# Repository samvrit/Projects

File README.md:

<h1>Projects</h1>
- <b>1-D Localization:</b> This is a 1-D Localization Problem. The map is given. User has to input the sensor values (0s and/or 1s). Once the robot figures out where it started, it will display the same. '3' is the starting point and '2' is the ending point. Accuracy of sensors/actuators is not considered in this algorithm (ie., probability of sensor and actuator are considered 1).   
- <b>Bluetooth-Controlled Modular Vehicle:</b> This is the software for a bluetooth-controlled modular vehicle (one main vehicle and two auxiliary vehicles).   
- <b>Certificates:</b> This directory contains a few important certificates.   
- <b>Electronic Dartboard:</b> This is a project aimed to develop an electronic dartboard which can output the score to a server every time a dart hits a target. The output is displayed on a remote computer.   
- <b>Grid Solving Robot:</b> An international level robotics competition held at IIT Bombay. The robot is given specific coordinates on a grid, to which it is supposed to navigate, and display the colour code of the surrounding four squares. The squares may have white colour or no colour, which the robot is supposed to indicate using four on-board LEDs.   
- <b>Line Follower using Image Processing</b>   
- <b>MATLAB Resultant Mass:</b> A MATLAB program to find the resultant mass for balancing of rotating masses on common axis (planar).   
- <b>Morse Code Reader Robot:</b> A national level robotics competition held at NIT-K Suratkal, Karnataka. The Robot is supposed to traverse a line containing several combinations of dots and dashes. A combination of five (dots and/or dashes) represents a number in Morse code. The robot is supposed to traverse the arena and add up all the numbers  represented in Morse code, and in the end, display the sum.   
- <b>PID Line Follower:</b> Line follower robot algorithm which uses PID to find the centre of the black line on a white background   
- <b>RFID Check-in System:</b> This project uses RFID tags to check-in a user into a database. This project can be applied to any area which requires checking-in at different places under the same Wi-Fi network.   
- <b>Supernumerary Robotic Limbs (Final Year Project):</b> Supernumerary Robotic Arms is a pair of low cost multi-purpose Robotic arms with 4 DoFs in each arm. The Robot is extendable in terms of functionality by attaching suitable end-effectors depending on the application. The actuators can be controlled wirelessly using nRF24L01 radio modules. Motion Planning is done using geometrically derived inverse kinematics. Mathematical Model and Simulations have been carried out using MATLAB Simulink and Robotics Toolbox for MATLAB. The robot description model (URDF) and the corresponding MoveIt! configuration package have also been developed for ROS. This project was funded by the IEEE University Partnership Program ($1500). Mentor: <a href="http://www.mecheng.iisc.ernet.in/~asitava/" target="_blank">Prof. Ashitava Ghosal</a>, IISc.

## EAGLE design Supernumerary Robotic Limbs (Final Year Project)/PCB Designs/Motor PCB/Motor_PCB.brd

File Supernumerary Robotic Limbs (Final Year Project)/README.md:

<h1>Supernumerary Robotic Limbs - Final Year Project</h1>
Supernumerary Robotic Arms is a pair of low cost multi-purpose Robotic arms with 4 DoFs in each arm. The Robot is extendable in terms of functionality by attaching suitable end-effectors depending on the application. The actuators can be controlled wirelessly using nRF24L01 radio modules. Motion Planning is done using geometrically derived inverse kinematics. Mathematical Model and Simulations have been carried out using MATLAB Simulink and Robotics Toolbox for MATLAB. The robot description model (URDF) and the corresponding MoveIt! configuration package have also been developed for ROS. This project was funded by the IEEE University Partnership Program ($1500). Mentor: <a href="http://www.mecheng.iisc.ernet.in/~asitava/" target="_blank">Prof. Ashitava Ghosal</a>, IISc.

A <a href="http://ieeexplore.ieee.org/xpl/articleDetails.jsp?arnumber=7283889" target="_blank">paper</a> was published on the mechanical design and kinematic model of the robot.

The robot is currently a stationary one, but it is intended to be a mobile platform, which can be worn by the user like a backpack.

Applications of this kind of robots can be seen in tasks that can be semi-automated, such as in assembly of aeroplanes, wiring of control boxes, etc.

The project was inspired by the work done by students of MIT under Prof. Harry Asada.

Videos:

1. <a href="https://www.youtube.com/watch?v=1jS6DkzcwM0" target="_blank">Robot in action</a>
2. <a href="https://www.youtube.com/watch?v=-V_I5MpTWcI" target="_blank">Robot Inverse Kinematics Simulation (MATLAB Robotics Toolbox)</a>
3. <a href="https://www.youtube.com/watch?v=2IG5NMGldtQ" target="_blank">Paper presentation on the project at the 20th International Conference on Methods and Models in Automation and Robotics</a>
4. <a href="https://www.youtube.com/watch?v=e1p7m6lmJI8" target="_blank">Robot writing the word "IISc"</a>

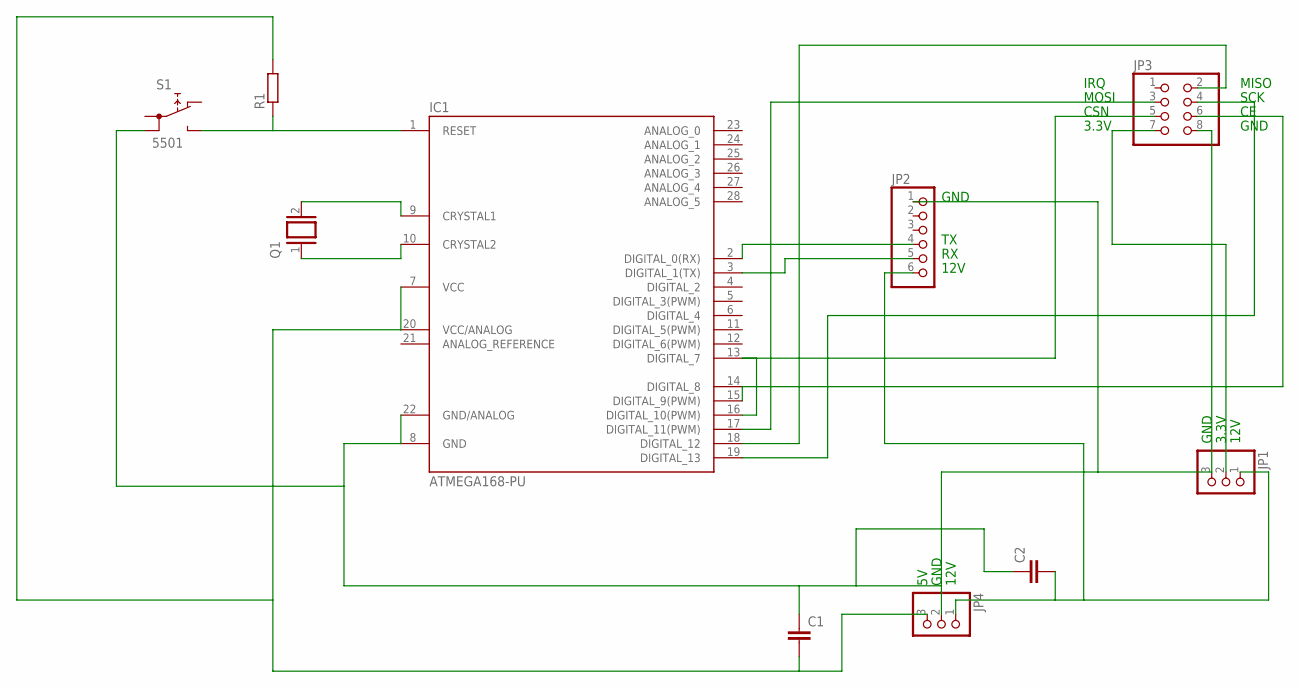
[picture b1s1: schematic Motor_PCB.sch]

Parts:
C1, C2: C2,5-3; C2.5-3
IC1: ATMEGA168-PU; DIL28-3
JP1, JP4: PINHD-1X3; 1X03
JP2: PINHD-1X6; 1X06
JP3: PINHD-2X4; 2X04
Q1: XTAL/S; QS
R1: R0207/10; 0207/10
S1: 5501

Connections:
unnamed: IC1.9 (CRYSTAL1), Q1.2
unnamed: IC1.10 (CRYSTAL2), Q1.1
unnamed: C1.2, IC1.7 (VCC), IC1.20 (VCC/ANALOG), JP4.3, R1.2
unnamed: C1.1, C2.1, IC1.8 (GND), IC1.22 (GND/ANALOG), JP1.3, JP2.1, JP3.8, JP4.2, S1.1B
unnamed: IC1.1 (RESET), R1.1, S1.NO
unnamed: C2.2, JP1.1, JP2.6, JP4.1
unnamed: IC1.17 (DIGITAL_11(PWM)), JP3.3
unnamed: IC1.18 (DIGITAL_12), JP3.2
unnamed: IC1.13 (DIGITAL_7), IC1.16 (DIGITAL_10(PWM)), JP3.5
unnamed: IC1.2 (DIGITAL_0(RX)), JP2.4
unnamed: IC1.3 (DIGITAL_1(TX)), JP2.5
unnamed: JP1.2, JP3.7
unnamed: IC1.14 (DIGITAL_8), IC1.15 (DIGITAL_9(PWM)), JP3.6
unnamed: IC1.19 (DIGITAL_13), JP3.4

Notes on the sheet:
12V
3.3V
GND
CSN
SCK
MOSI
MISO
IRQ

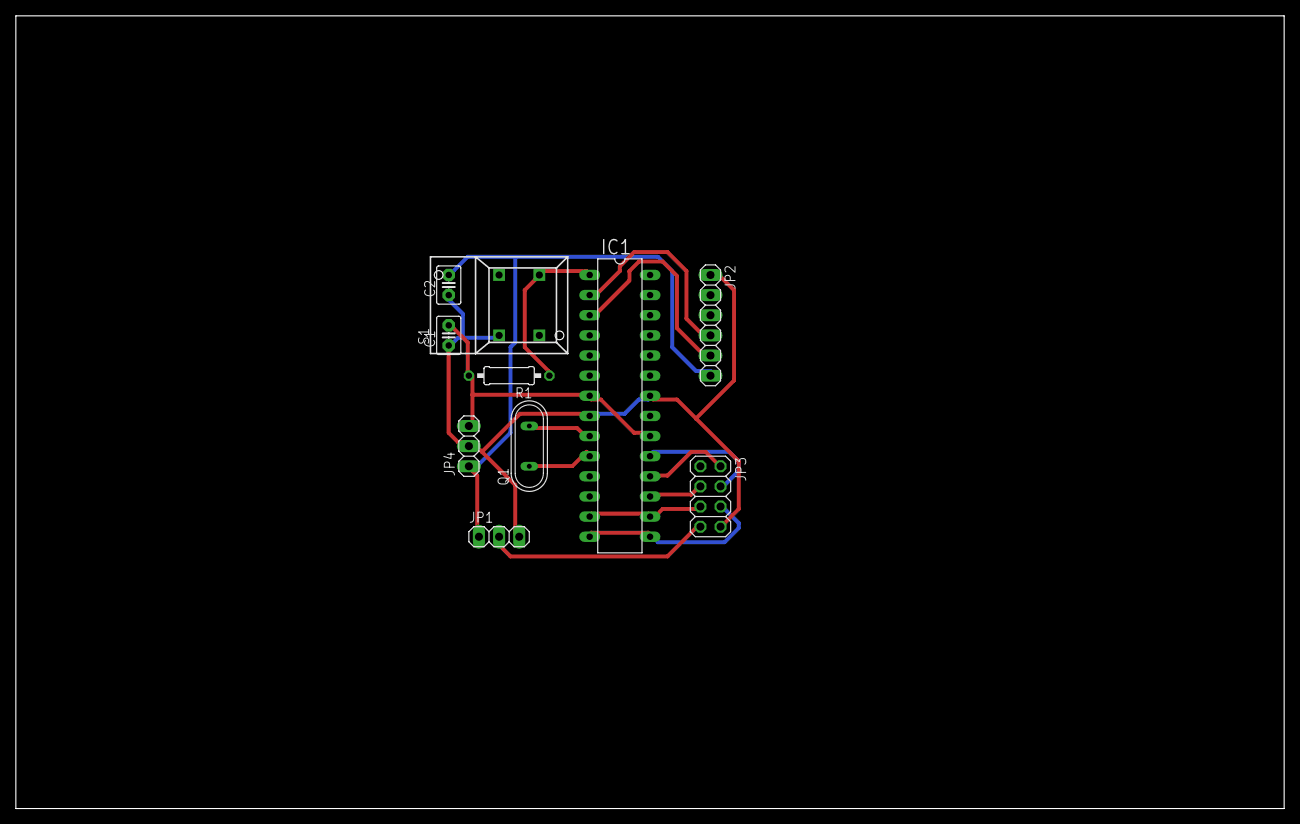
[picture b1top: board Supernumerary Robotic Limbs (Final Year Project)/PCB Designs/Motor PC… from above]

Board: 2 copper layers, 160.0 x 100.0 mm, 10 parts (0 on the bottom side), 14 nets.

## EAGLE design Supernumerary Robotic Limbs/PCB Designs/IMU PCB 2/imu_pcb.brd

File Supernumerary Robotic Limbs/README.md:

Supernumerary Robotic Arms is a pair of low cost multi-purpose Robotic arms with 4 DoFs in each arm. The Robot is extendable in terms of functionality by attaching suitable end-effectors depending on the application. The actuators can be controlled wirelessly using NRF24L01 radio modules. Motion Planning is done using geometrically derived inverse kinematics. Mathematical Model and Simulations have been carried out using MATLAB Simulink and Robotics Toolbox for MATLAB.  This project was funded by the IEEE University Partnership Program ($1500).

The robot is currently a stationary one, but it is intended to be a mobile platform, which can be worn by the user like a backpack.

Applications of this kind of robots can be seen in tasks that can be semi-automated, such as in assembly of aeroplanes, wiring of control boxes, etc.

The project was inspired by the work done by students of MIT under Prof. Harry Asada.

Videos:

1. Robot in action: https://www.youtube.com/watch?v=1jS6DkzcwM0
2. Robot Inverse Kinematics Simulation (MATLAB Robotics Toolbox): https://www.youtube.com/watch?v=-V_I5MpTWcI
3. Paper presentation on the project at the 20th International Conference on Methods and Models in Automation and Robotics: https://www.youtube.com/watch?v=2IG5NMGldtQ

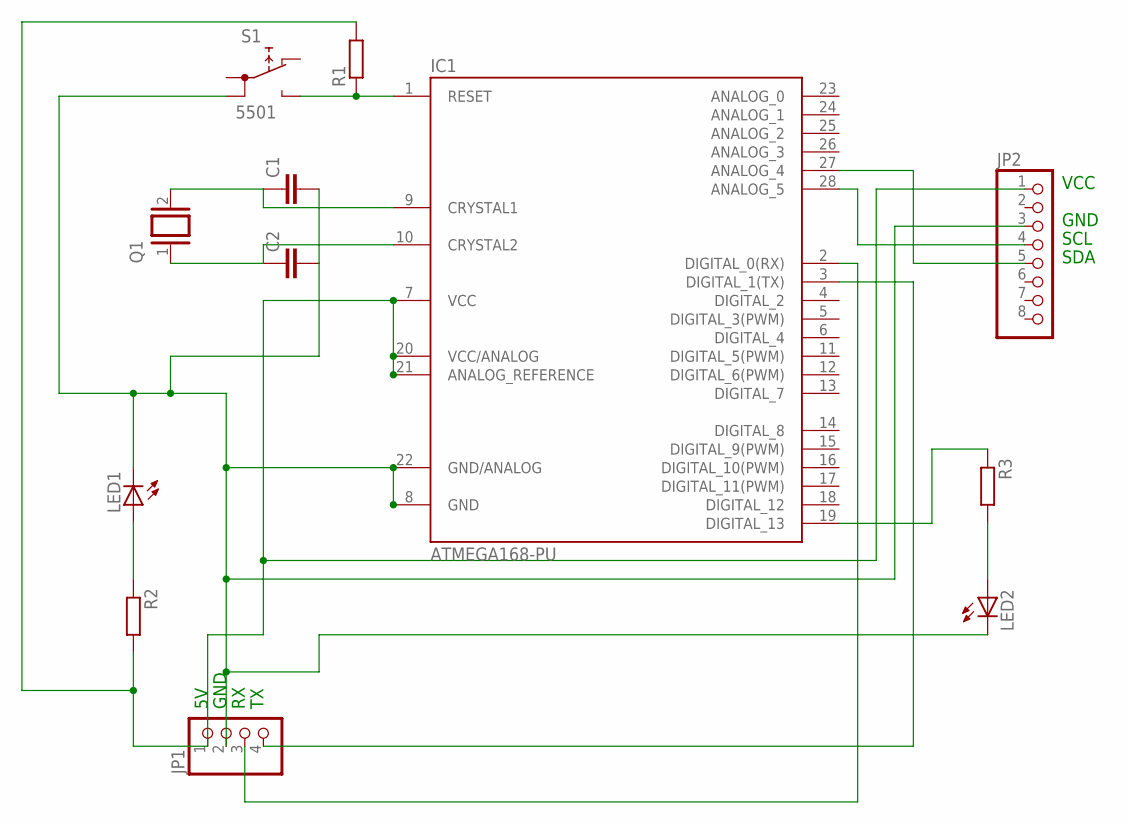
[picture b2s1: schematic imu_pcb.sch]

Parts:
C1, C2: C2.5/2; C2.5-2
IC1: ATMEGA168-PU; DIL28-3
JP1: PINHD-1X4; 1X04
JP2: PINHD-1X8; 1X08
LED1, LED2: LED3MM
Q1: XTAL/S; QS
R1, R2, R3: R0204/7; 0204/7
S1: 5501

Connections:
unnamed: IC1.1 (RESET), R1.1, S1.NO
unnamed: IC1.7 (VCC), IC1.20 (VCC/ANALOG), IC1.21 (ANALOG_REFERENCE), JP1.1, JP2.1, R1.2, R2.2
unnamed: LED1.A, R2.1
unnamed: C1.1, IC1.9 (CRYSTAL1), Q1.2
unnamed: C2.1, IC1.10 (CRYSTAL2), Q1.1
unnamed: IC1.2 (DIGITAL_0(RX)), JP1.3
unnamed: IC1.3 (DIGITAL_1(TX)), JP1.4
unnamed: C1.2, C2.2, IC1.8 (GND), IC1.22 (GND/ANALOG), JP1.2, JP2.3, LED1.K (C), LED2.K (C), S1.1B
unnamed: IC1.27 (ANALOG_4), JP2.5
unnamed: IC1.28 (ANALOG_5), JP2.4
unnamed: IC1.19 (DIGITAL_13), R3.1
unnamed: LED2.A, R3.2

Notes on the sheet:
GND
VCC
SCL
SDA

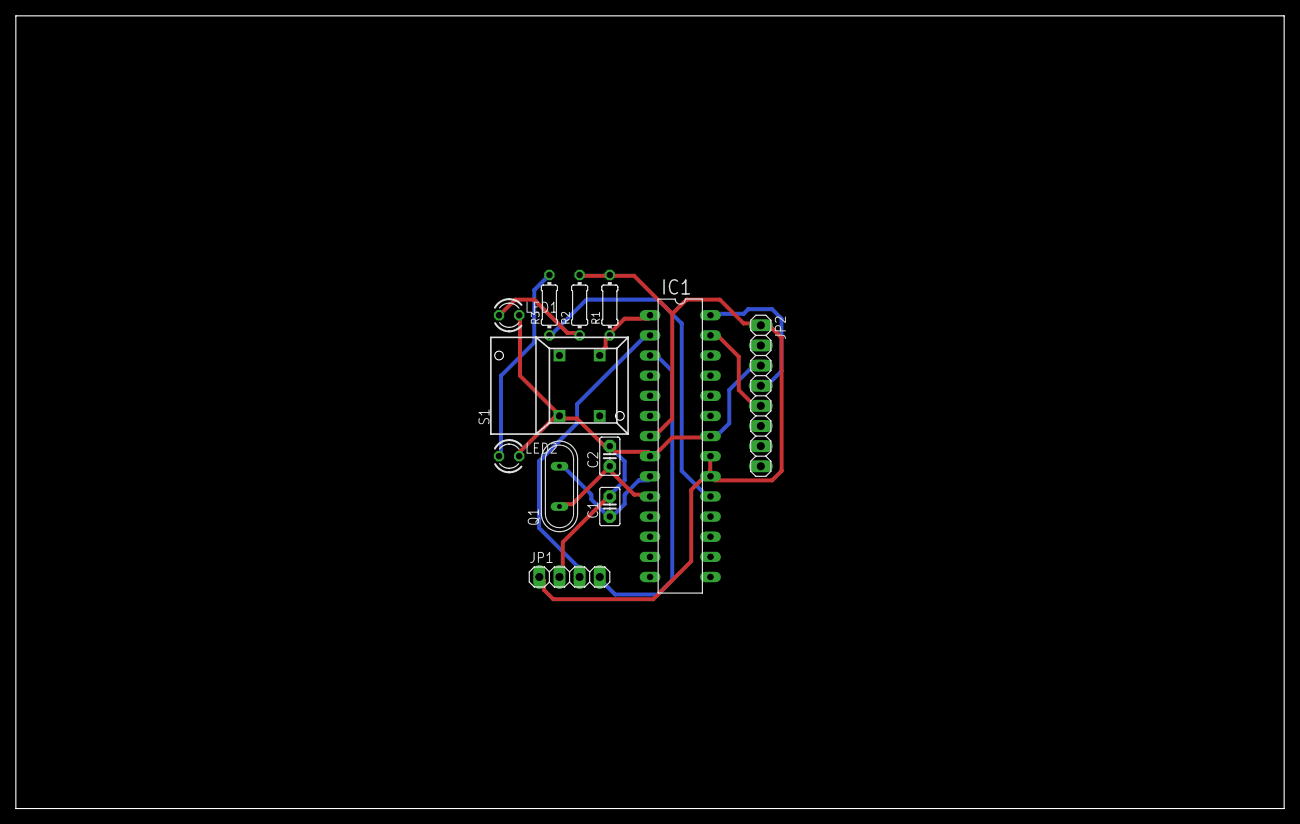
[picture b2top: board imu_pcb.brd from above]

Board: 2 copper layers, 160.0 x 100.0 mm, 12 parts (0 on the bottom side), 12 nets.

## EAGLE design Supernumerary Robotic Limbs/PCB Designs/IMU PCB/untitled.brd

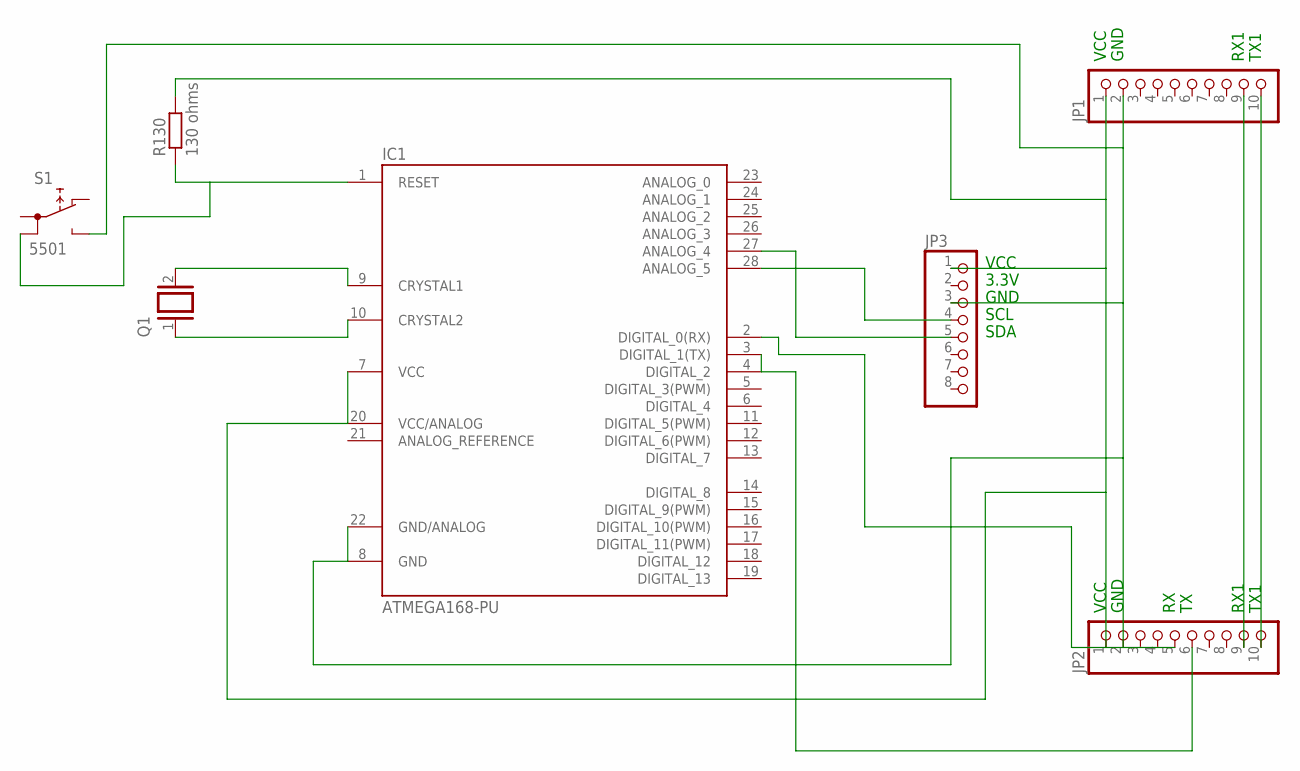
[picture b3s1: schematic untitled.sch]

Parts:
IC1: ATMEGA168-PU; DIL28-3
JP1, JP2: PINHD-1X10; 1X10
JP3: PINHD-1X8; 1X08
Q1: XTAL/S; QS
R130: 130 ohms; 0204/7
S1: 5501

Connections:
unnamed: IC1.1 (RESET), R130.1, S1.1B
unnamed: IC1.7 (VCC), IC1.20 (VCC/ANALOG), JP1.1, JP2.1, JP3.1, R130.2
unnamed: IC1.8 (GND), IC1.22 (GND/ANALOG), JP1.2, JP2.2, JP3.3, S1.NO
unnamed: JP1.9, JP2.9
unnamed: JP1.10, JP2.10
unnamed: IC1.28 (ANALOG_5), JP3.4
unnamed: IC1.27 (ANALOG_4), JP3.5
unnamed: IC1.9 (CRYSTAL1), Q1.2
unnamed: IC1.10 (CRYSTAL2), Q1.1
unnamed: IC1.2 (DIGITAL_0(RX)), JP2.5
unnamed: IC1.3 (DIGITAL_1(TX)), JP2.6

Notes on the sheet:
VCC
GND
RX1
TX1
3.3V
SCL
SDA

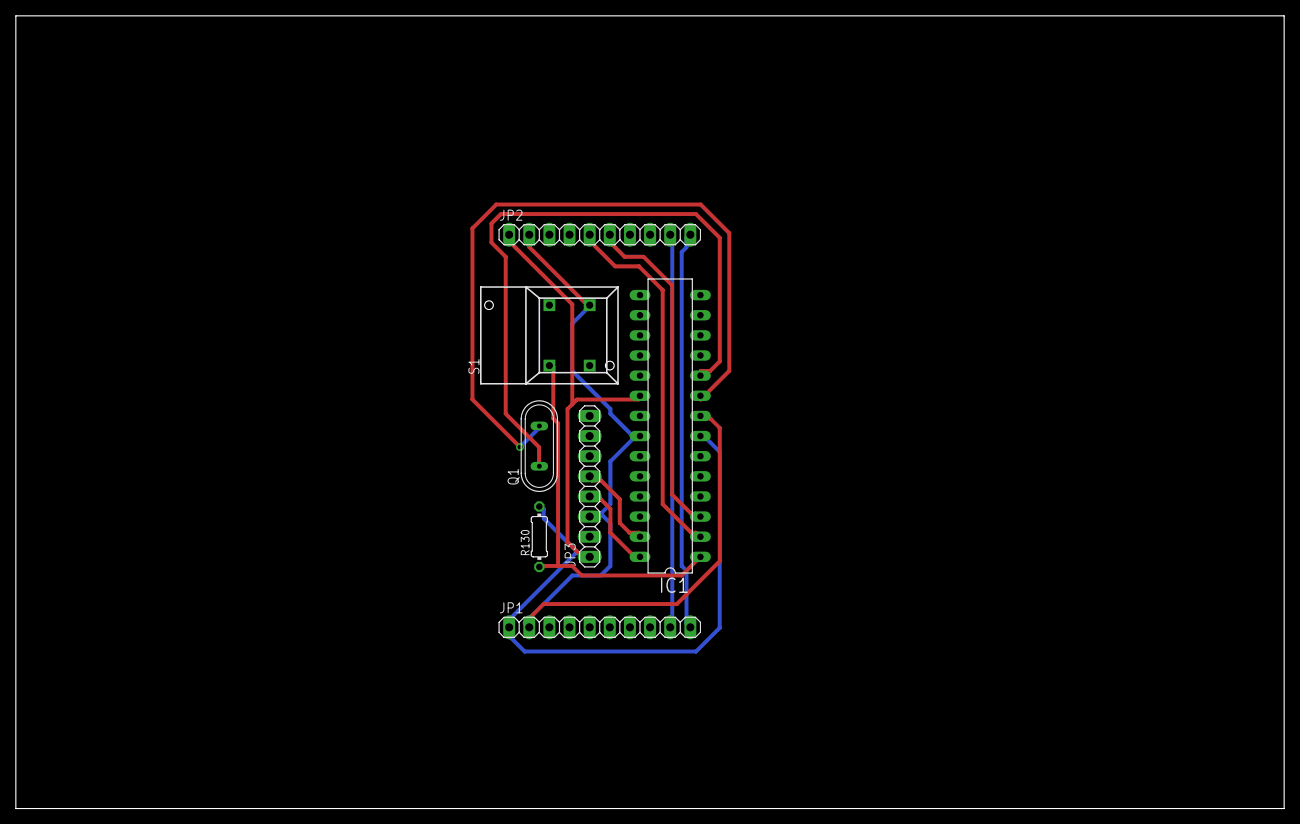
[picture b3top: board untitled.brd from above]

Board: 2 copper layers, 160.0 x 100.0 mm, 7 parts (0 on the bottom side), 11 nets.

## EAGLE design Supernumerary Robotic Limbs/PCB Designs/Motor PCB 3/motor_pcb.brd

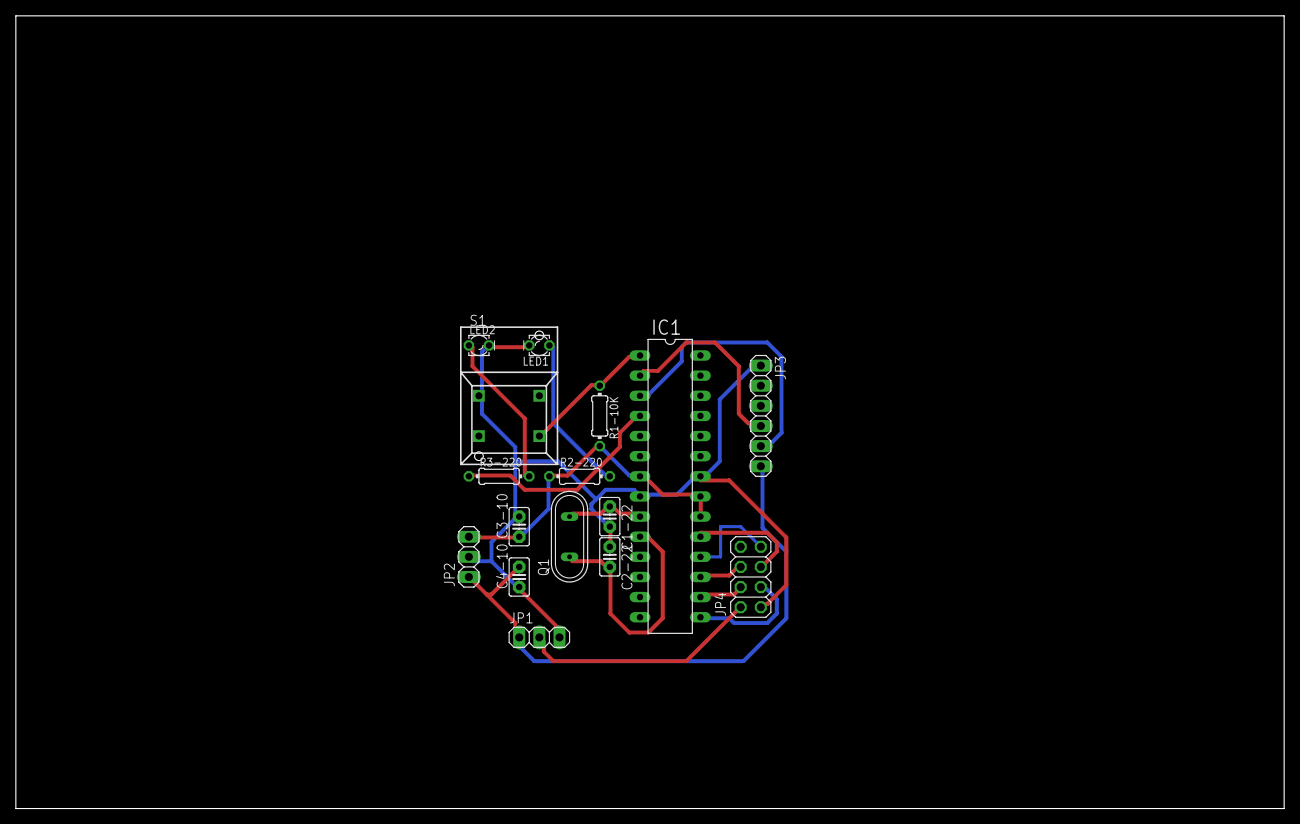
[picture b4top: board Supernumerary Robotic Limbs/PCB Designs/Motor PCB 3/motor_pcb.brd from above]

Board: 2 copper layers, 160.0 x 100.0 mm, 16 parts (0 on the bottom side), 17 nets.

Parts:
C1-22, C2-22, C3-10, C4-10: C2.5-2
IC1: ATMEGA168-PU; DIL28-3
JP1, JP2: 1X03
JP3: 1X06
JP4: 2X04
LED1, LED2: LED_LD260
Q1: QS
R1-10K, R2-220, R3-220: 0204/7
S1: 5501

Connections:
unnamed: IC1.1, R1-10K.1, S1.NO
unnamed: C1-22.2, C2-22.1, C3-10.2, C4-10.1, IC1.8, IC1.22, JP1.3, JP2.2, JP3.1, JP4.1, LED1.K, LED2.K, S1.1B
unnamed: C1-22.1, IC1.9, Q1.2
unnamed: C2-22.2, IC1.10, Q1.1
unnamed: C4-10.2, JP1.1, JP2.1, JP3.6
unnamed: JP1.2, JP4.2
unnamed: C3-10.1, IC1.7, IC1.20, IC1.21, JP2.3, R1-10K.2, R2-220.1
unnamed: IC1.3, JP3.5
unnamed: IC1.15, JP4.3
unnamed: IC1.16, JP4.4
unnamed: IC1.19, JP4.5
unnamed: IC1.17, JP4.6
unnamed: IC1.18, JP4.7
unnamed: IC1.2, JP3.4
unnamed: LED1.A, R2-220.2
unnamed: IC1.4, R3-220.1
unnamed: LED2.A, R3-220.2

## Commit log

2015-09-16 :space_invader: Added .gitattributes & .gitignore files
2015-09-16 Supernumerary Robotic Limbs
2015-09-16 Project Report
2015-09-17 Published Paper
2015-09-18 readme
2015-09-20 Projects
2015-10-16 Project
2015-11-09 Projects & Certificates
2016-03-16 Projects:
2016-08-17 bluetooth project
2016-11-27 kinematic analysis
2016-11-27 kinematic
2016-12-06 spherical wrist
2016-12-31 report
